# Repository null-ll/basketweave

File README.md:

# Basketweave

Through-hole Alice-style keyboard with arrow keys and a rotary encoder

### Default Layout

> View on [Keyboard Layout Editor](http://www.keyboard-layout-editor.com/#/gists/9b58a2c896b3cc25a28ef1dc43d93095) - for reference only

### BOM and Build Guide
[Build Guide](doc/build.md)

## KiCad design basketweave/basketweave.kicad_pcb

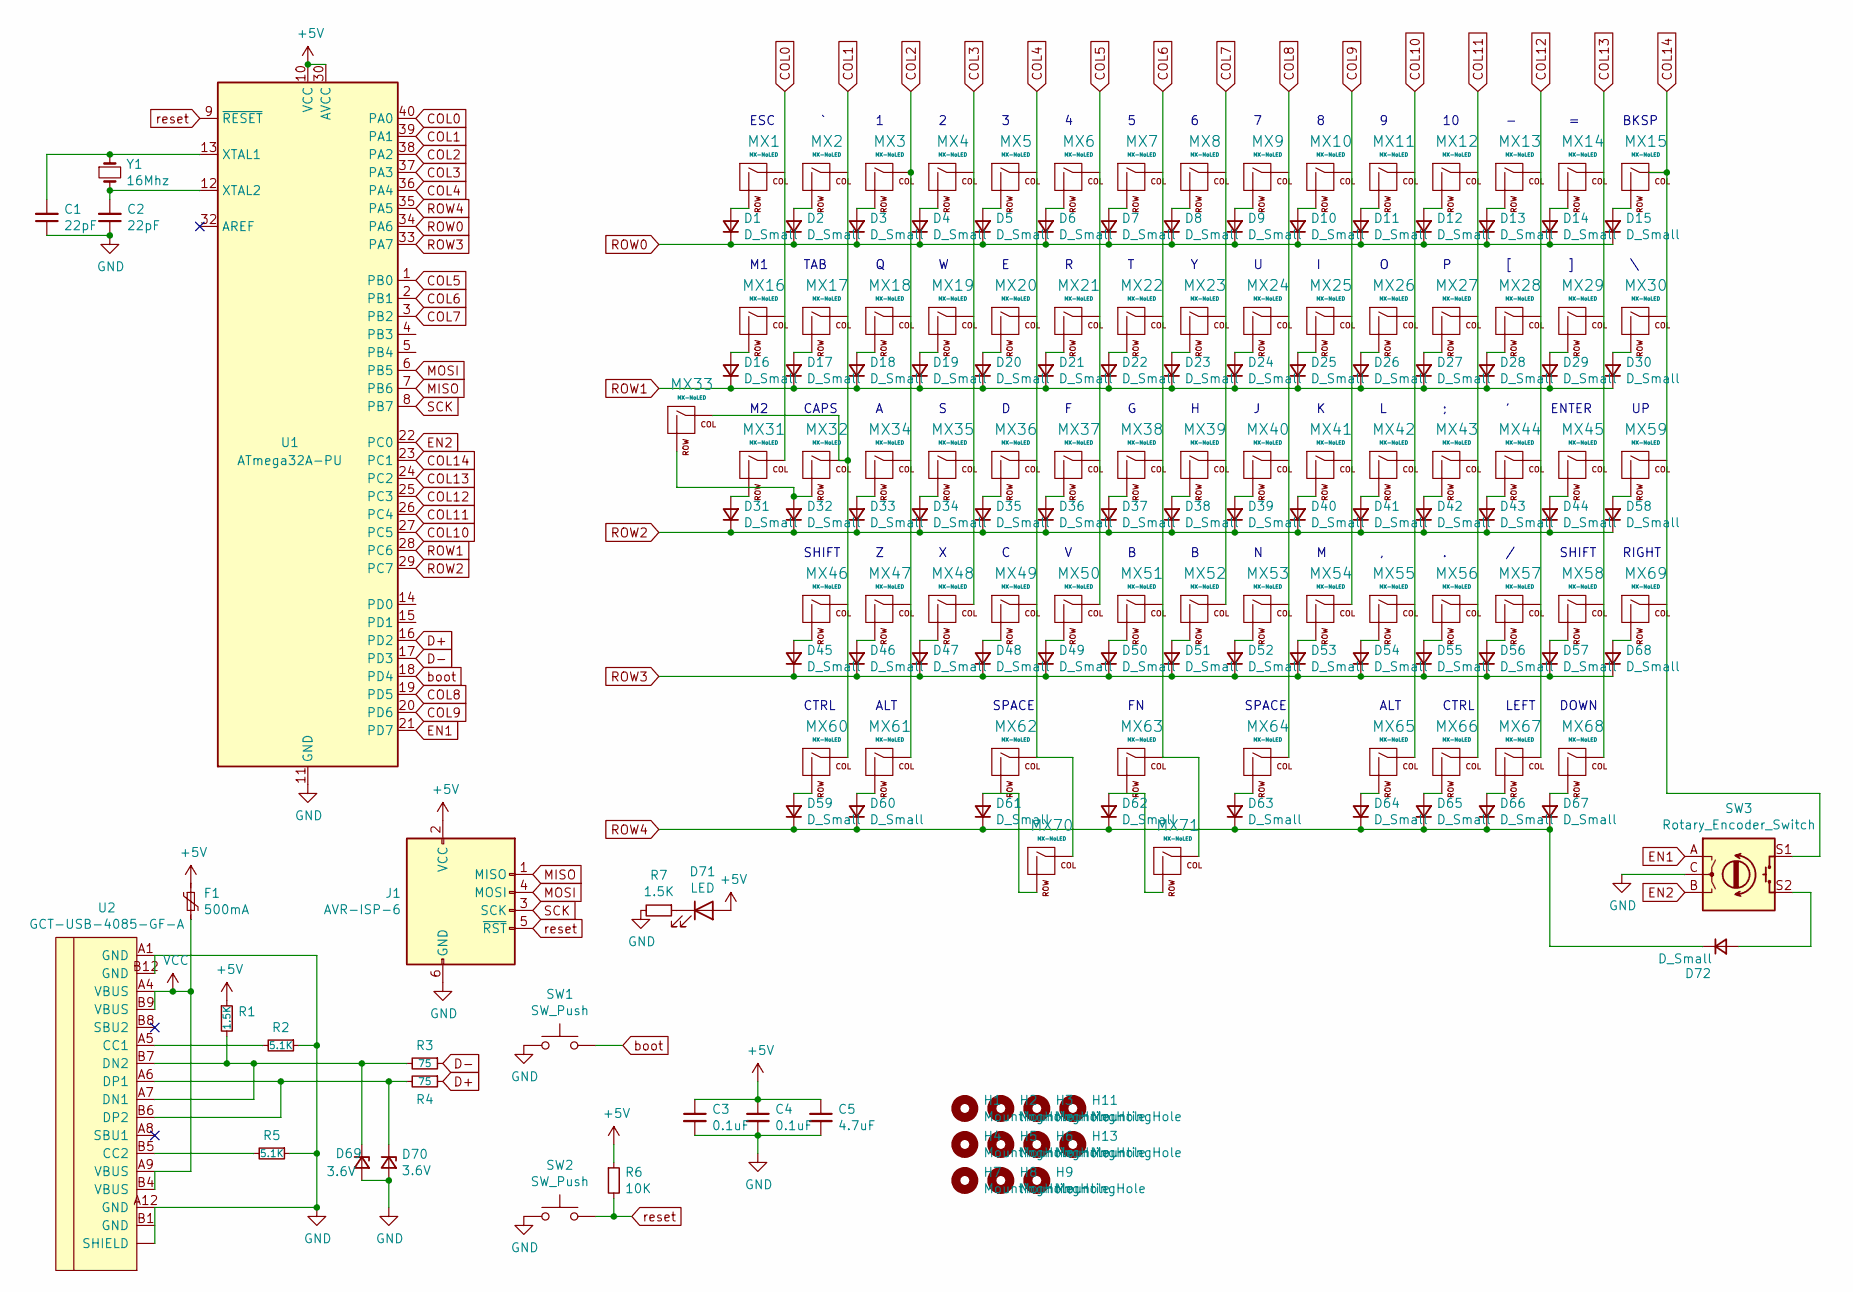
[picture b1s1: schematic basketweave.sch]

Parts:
C1, C2: 22pF; C_Disc_D3.0mm_W2.0mm_P2.50mm
C3, C4: 0.1uF; C_Disc_D4.3mm_W1.9mm_P5.00mm
C5: 4.7uF; CP_Radial_D4.0mm_P1.50mm
D1, D2, D3, D4, D5, D6, D7, D8, D9, D10, D11, D12, D13, D14, D15, D16, D17, D18, D19, D20, D21, D22, D23, D24, D25, D26, D27, D28, D29, D30, D31, D32, D33, D34, D35, D36, D37, D38, D39, D40, D41, D42, D43, D44, D45, D46, D47, D48, D49, D50, D51, D52, D53, D54, D55, D56, D57, D58, D59, D60, D61, D62, D63, D64, D65, D66, D67, D68, D72: D_Small; D_DO-35_SOD27_P7.62mm_Horizontal
D69, D70: 3.6V; D_DO-35_SOD27_P7.62mm_Horizontal
D71: LED; LED_D3.0mm_Clear
F1: 500mA; polyfuse_5.1mm
H1, H2, H3, H4, H5, H6, H7, H8, H9, H11, H13: MountingHole; MountingHole_2.2mm_M2_Pad
J1: AVR-ISP-6; PinHeader_2x03_P2.54mm_Vertical
MX1, MX2, MX3, MX4, MX5, MX6, MX7, MX8, MX9, MX10, MX11, MX12, MX13, MX14, MX16, MX18, MX19, MX20, MX21, MX22, MX23, MX24, MX25, MX26, MX27, MX28, MX29, MX31, MX34, MX35, MX36, MX37, MX38, MX39, MX40, MX41, MX42, MX43, MX44, MX47, MX48, MX49, MX50, MX51, MX52, MX53, MX54, MX55, MX56, MX57, MX59, MX67, MX68, MX69, MX71: MX-NoLED; MXOnly-1U-NoLED
MX15: MX-NoLED; MXOnly-2U-NoLED
MX17, MX30, MX60, MX61, MX65, MX66: MX-NoLED; MXOnly-1.5U-NoLED
MX32, MX63: MX-NoLED; MXOnly-1.25U-NoLED
MX33, MX58: MX-NoLED; MXOnly-1.75U-NoLED
MX45, MX46, MX70: MX-NoLED; MXOnly-2.25U-ReversedStabilizers-NoLED
MX62: MX-NoLED; MXOnly-2U-ReversedStabilizers-NoLED
MX64: MX-NoLED; MXOnly-2.75U-ReversedStabilizers-NoLED
R1, R7: 1.5K; R_Axial_DIN0204_L3.6mm_D1.6mm_P5.08mm_Horizontal
R2, R5: 5.1K; R_Axial_DIN0204_L3.6mm_D1.6mm_P5.08mm_Horizontal
R3, R4: 75; R_Axial_DIN0204_L3.6mm_D1.6mm_P5.08mm_Horizontal
R6: 10K; R_Axial_DIN0204_L3.6mm_D1.6mm_P5.08mm_Horizontal
SW1, SW2: SW_Push; SW_PUSH_6mm
SW3: Rotary_Encoder_Switch; RotaryEncoder_Alps_EC11E-Switch_Vertical_H20mm
U1: ATmega32A-PU; DIP-40_W15.24mm
U2: GCT-USB-4085-GF-A; USB_C_GCT_USB4085
Y1: 16Mhz; Crystal_HC49-4H_Vertical

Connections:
COL0: MX1.1 (COL), MX16.1 (COL), MX31.1 (COL), U1.40 (PA0)
COL1: MX2.1 (COL), MX17.1 (COL), MX32.1 (COL), MX33.1 (COL), MX46.1 (COL), MX60.1 (COL), U1.39 (PA1)
COL2: MX3.1 (COL), MX18.1 (COL), MX34.1 (COL), MX47.1 (COL), MX61.1 (COL), U1.38 (PA2)
COL3: MX4.1 (COL), MX19.1 (COL), MX35.1 (COL), MX48.1 (COL), U1.37 (PA3)
COL4: MX5.1 (COL), MX20.1 (COL), MX36.1 (COL), MX49.1 (COL), MX62.1 (COL), MX70.1 (COL), U1.36 (PA4)
COL5: MX6.1 (COL), MX21.1 (COL), MX37.1 (COL), MX50.1 (COL), U1.1 (PB0)
COL6: MX7.1 (COL), MX22.1 (COL), MX38.1 (COL), MX51.1 (COL), MX63.1 (COL), MX71.1 (COL), U1.2 (PB1)
COL7: MX8.1 (COL), MX23.1 (COL), MX39.1 (COL), MX52.1 (COL), U1.3 (PB2)
COL8: MX9.1 (COL), MX24.1 (COL), MX40.1 (COL), MX53.1 (COL), MX64.1 (COL), U1.19 (PD5)
COL9: MX10.1 (COL), MX25.1 (COL), MX41.1 (COL), MX54.1 (COL), U1.20 (PD6)
COL10: MX11.1 (COL), MX26.1 (COL), MX42.1 (COL), MX55.1 (COL), MX65.1 (COL), U1.27 (PC5)
COL11: MX12.1 (COL), MX27.1 (COL), MX43.1 (COL), MX56.1 (COL), MX66.1 (COL), U1.26 (PC4)
COL12: MX13.1 (COL), MX28.1 (COL), MX44.1 (COL), MX57.1 (COL), MX67.1 (COL), U1.25 (PC3)
COL13: MX14.1 (COL), MX29.1 (COL), MX45.1 (COL), MX58.1 (COL), MX68.1 (COL), U1.24 (PC2)
COL14: MX15.1 (COL), MX30.1 (COL), MX59.1 (COL), MX69.1 (COL), SW3.S1, U1.23 (PC1); also elsewhere on the board
D+: R4.1, U1.16 (PD2)
D-: R3.1, U1.17 (PD3)
EN1: SW3.A, U1.21 (PD7); also elsewhere on the board
EN2: SW3.B, U1.22 (PC0); also elsewhere on the board
GND: C1.1, C2.1, C3.2, C4.2, C5.2, D69.2 (A), D70.2 (A), J1.6 (GND), R2.1, R5.1, R7.2, SW1.1, SW2.1, SW3.C, U1.11 (GND), U1.31 (GND), U2.A1 (GND), U2.A12 (GND), U2.B12 (GND), U2.~ (SHIELD); also elsewhere on the board
MISO: J1.1 (MISO), U1.7 (PB6); also elsewhere on the board
MOSI: J1.4 (MOSI), U1.6 (PB5); also elsewhere on the board
unnamed: C1.2, U1.13 (XTAL1), Y1.1
unnamed: C2.2, U1.12 (XTAL2), Y1.2
unnamed: D1.2 (A), MX1.2 (ROW)
unnamed: D2.2 (A), MX2.2 (ROW)
unnamed: D3.2 (A), MX3.2 (ROW)
unnamed: D4.2 (A), MX4.2 (ROW)
unnamed: D5.2 (A), MX5.2 (ROW)
unnamed: D6.2 (A), MX6.2 (ROW)
unnamed: D7.2 (A), MX7.2 (ROW)
unnamed: D8.2 (A), MX8.2 (ROW)
unnamed: D9.2 (A), MX9.2 (ROW)
unnamed: D10.2 (A), MX10.2 (ROW)
unnamed: D11.2 (A), MX11.2 (ROW)
unnamed: D12.2 (A), MX12.2 (ROW)
unnamed: D13.2 (A), MX13.2 (ROW)
unnamed: D14.2 (A), MX14.2 (ROW)
unnamed: D15.2 (A), MX15.2 (ROW)
unnamed: D16.2 (A), MX16.2 (ROW)
unnamed: D17.2 (A), MX17.2 (ROW)
unnamed: D18.2 (A), MX18.2 (ROW)
unnamed: D19.2 (A), MX19.2 (ROW)
unnamed: D20.2 (A), MX20.2 (ROW)
unnamed: D21.2 (A), MX21.2 (ROW)
unnamed: D22.2 (A), MX22.2 (ROW)
unnamed: D23.2 (A), MX23.2 (ROW)
unnamed: D24.2 (A), MX24.2 (ROW)
unnamed: D25.2 (A), MX25.2 (ROW)
unnamed: D26.2 (A), MX26.2 (ROW)
unnamed: D27.2 (A), MX27.2 (ROW)
unnamed: D28.2 (A), MX28.2 (ROW)
unnamed: D29.2 (A), MX29.2 (ROW)
unnamed: D30.2 (A), MX30.2 (ROW)
unnamed: D31.2 (A), MX31.2 (ROW)
unnamed: D32.2 (A), MX32.2 (ROW), MX33.2 (ROW)
unnamed: D33.2 (A), MX34.2 (ROW)
unnamed: D34.2 (A), MX35.2 (ROW)
unnamed: D35.2 (A), MX36.2 (ROW)
unnamed: D36.2 (A), MX37.2 (ROW)
unnamed: D37.2 (A), MX38.2 (ROW)
unnamed: D38.2 (A), MX39.2 (ROW)
unnamed: D39.2 (A), MX40.2 (ROW)
unnamed: D40.2 (A), MX41.2 (ROW)
unnamed: D41.2 (A), MX42.2 (ROW)
unnamed: D42.2 (A), MX43.2 (ROW)
unnamed: D43.2 (A), MX44.2 (ROW)
unnamed: D44.2 (A), MX45.2 (ROW)
unnamed: D45.2 (A), MX46.2 (ROW)
unnamed: D46.2 (A), MX47.2 (ROW)
unnamed: D47.2 (A), MX48.2 (ROW)
unnamed: D48.2 (A), MX49.2 (ROW)
unnamed: D49.2 (A), MX50.2 (ROW)
unnamed: D50.2 (A), MX51.2 (ROW)
unnamed: D51.2 (A), MX52.2 (ROW)
unnamed: D52.2 (A), MX53.2 (ROW)
unnamed: D53.2 (A), MX54.2 (ROW)
unnamed: D54.2 (A), MX55.2 (ROW)
unnamed: D55.2 (A), MX56.2 (ROW)
unnamed: D56.2 (A), MX57.2 (ROW)
unnamed: D57.2 (A), MX58.2 (ROW)
unnamed: D58.2 (A), MX59.2 (ROW)
unnamed: D59.2 (A), MX60.2 (ROW)
unnamed: D60.2 (A), MX61.2 (ROW)
unnamed: D63.2 (A), MX64.2 (ROW)
unnamed: D64.2 (A), MX65.2 (ROW)
unnamed: D65.2 (A), MX66.2 (ROW)
unnamed: D66.2 (A), MX67.2 (ROW)
unnamed: D67.2 (A), MX68.2 (ROW)
unnamed: D68.2 (A), MX69.2 (ROW)
unnamed 90: D69.1 (K), R1.2, R3.2, U2.A7 (DN1), U2.B7 (DN2); also elsewhere on the board
unnamed 91: D70.1 (K), R4.2, U2.A6 (DP1), U2.B6 (DP2); also elsewhere on the board
unnamed 92: R2.2, U2.A5 (CC1); also elsewhere on the board
unnamed 93: R5.2, U2.B5 (CC2); also elsewhere on the board
ROW0: D1.1 (K), D2.1 (K), D3.1 (K), D4.1 (K), D5.1 (K), D6.1 (K), D7.1 (K), D8.1 (K), D9.1 (K), D10.1 (K), D11.1 (K), D12.1 (K), D13.1 (K), D14.1 (K), D15.1 (K), U1.34 (PA6)
ROW1: D16.1 (K), D17.1 (K), D18.1 (K), D19.1 (K), D20.1 (K), D21.1 (K), D22.1 (K), D23.1 (K), D24.1 (K), D25.1 (K), D26.1 (K), D27.1 (K), D28.1 (K), D29.1 (K), D30.1 (K), U1.28 (PC6)
ROW2: D31.1 (K), D32.1 (K), D33.1 (K), D34.1 (K), D35.1 (K), D36.1 (K), D37.1 (K), D38.1 (K), D39.1 (K), D40.1 (K), D41.1 (K), D42.1 (K), D43.1 (K), D44.1 (K), D58.1 (K), U1.29 (PC7)
ROW3: D45.1 (K), D46.1 (K), D47.1 (K), D48.1 (K), D49.1 (K), D50.1 (K), D51.1 (K), D52.1 (K), D53.1 (K), D54.1 (K), D55.1 (K), D56.1 (K), D57.1 (K), D68.1 (K), U1.33 (PA7)
SCK: J1.3 (SCK), U1.8 (PB7); also elsewhere on the board
VCC: F1.2, U2.A4 (VBUS), U2.A9 (VBUS), U2.B4 (VBUS), U2.B9 (VBUS); also elsewhere on the board
boot: SW1.2, U1.18 (PD4); also elsewhere on the board
reset: J1.5 (~RST), R6.2, SW2.2, U1.9 (~RESET); also elsewhere on the board

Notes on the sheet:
ESC
BKSP
ENTER
CAPS
SHIFT
CTRL
ALT
SPACE
LEFT
DOWN
RIGHT
TAB

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
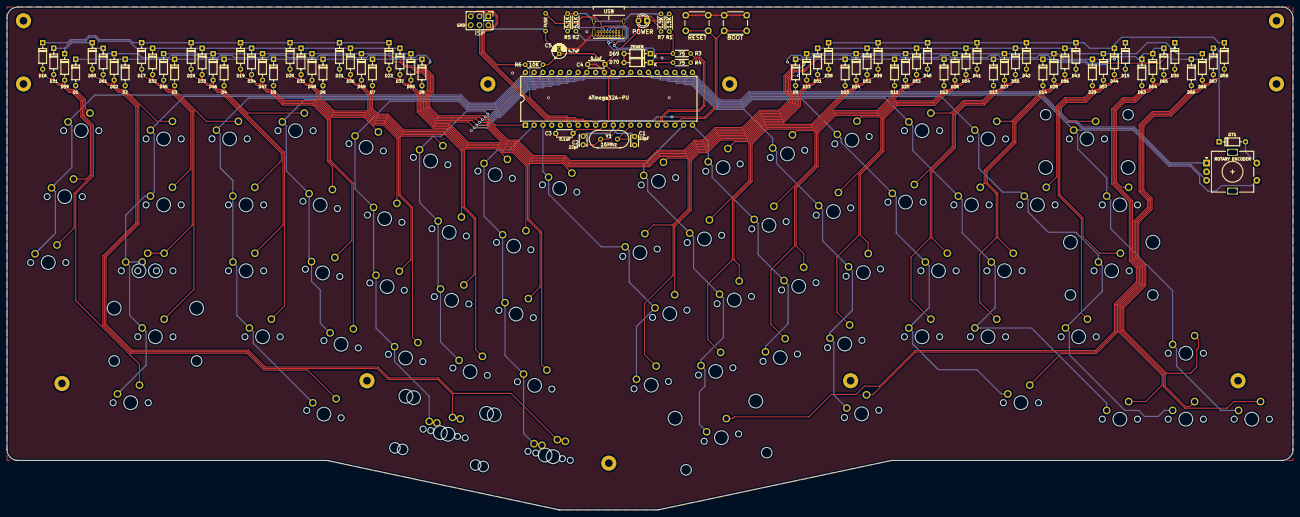
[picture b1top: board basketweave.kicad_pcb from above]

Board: 2 copper layers, 371.5 x 145.3 mm, 174 parts (0 on the bottom side), 108 nets.

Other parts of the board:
BOOT: SW_Push; SW_PUSH_6mm
ISP: AVR-ISP-6; PinHeader_2x03_P2.54mm_Vertical
POWER: LED; LED_D3.0mm_Clear
RESET: SW_Push; SW_PUSH_6mm
ROTARY ENCODER: Rotary_Encoder_Switch; RotaryEncoder_Alps_EC11E-Switch_Vertical_H20mm
USB: GCT-USB-4085-GF-A; USB_C_GCT_USB4085

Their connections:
COL14: ROTARY ENCODER.S1; also elsewhere on the board
EN1: ROTARY ENCODER.A; also elsewhere on the board
EN2: ROTARY ENCODER.B; also elsewhere on the board
GND: BOOT.1, ISP.6, RESET.1, ROTARY ENCODER.C, USB.A1, USB.A12, USB.B1, USB.B12, USB.S1; also elsewhere on the board
MISO: ISP.1; also elsewhere on the board
MOSI: ISP.4; also elsewhere on the board
unnamed 90: USB.A7, USB.B7; also elsewhere on the board
unnamed 91: USB.A6, USB.B6; also elsewhere on the board
unnamed 92: USB.A5; also elsewhere on the board
unnamed 93: USB.B5; also elsewhere on the board
SCK: ISP.3; also elsewhere on the board
VCC: USB.A4, USB.A9, USB.B4, USB.B9; also elsewhere on the board
boot: BOOT.2; also elsewhere on the board
reset: ISP.5, RESET.2; also elsewhere on the board

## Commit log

2020-09-20 added all files
2020-09-29 added picture
2020-10-01 Create LICENSE
2020-10-18 renamed to 'basketweave'
2020-10-24 changed logo, name, and pattern design
2020-10-24 added switch size markings
2020-11-04 added diode for rotary encoder switch
2020-12-02 Added acrylic guard
2021-01-03 removed unnecessary files
2021-01-10 fixed missing symbols
2021-01-23 fix sch
2021-07-23 fixed inaccurate label
2021-07-23 fixed typo
2022-03-11 Fix typo
2022-06-15 Add note about resistor sizing and capacitor type
